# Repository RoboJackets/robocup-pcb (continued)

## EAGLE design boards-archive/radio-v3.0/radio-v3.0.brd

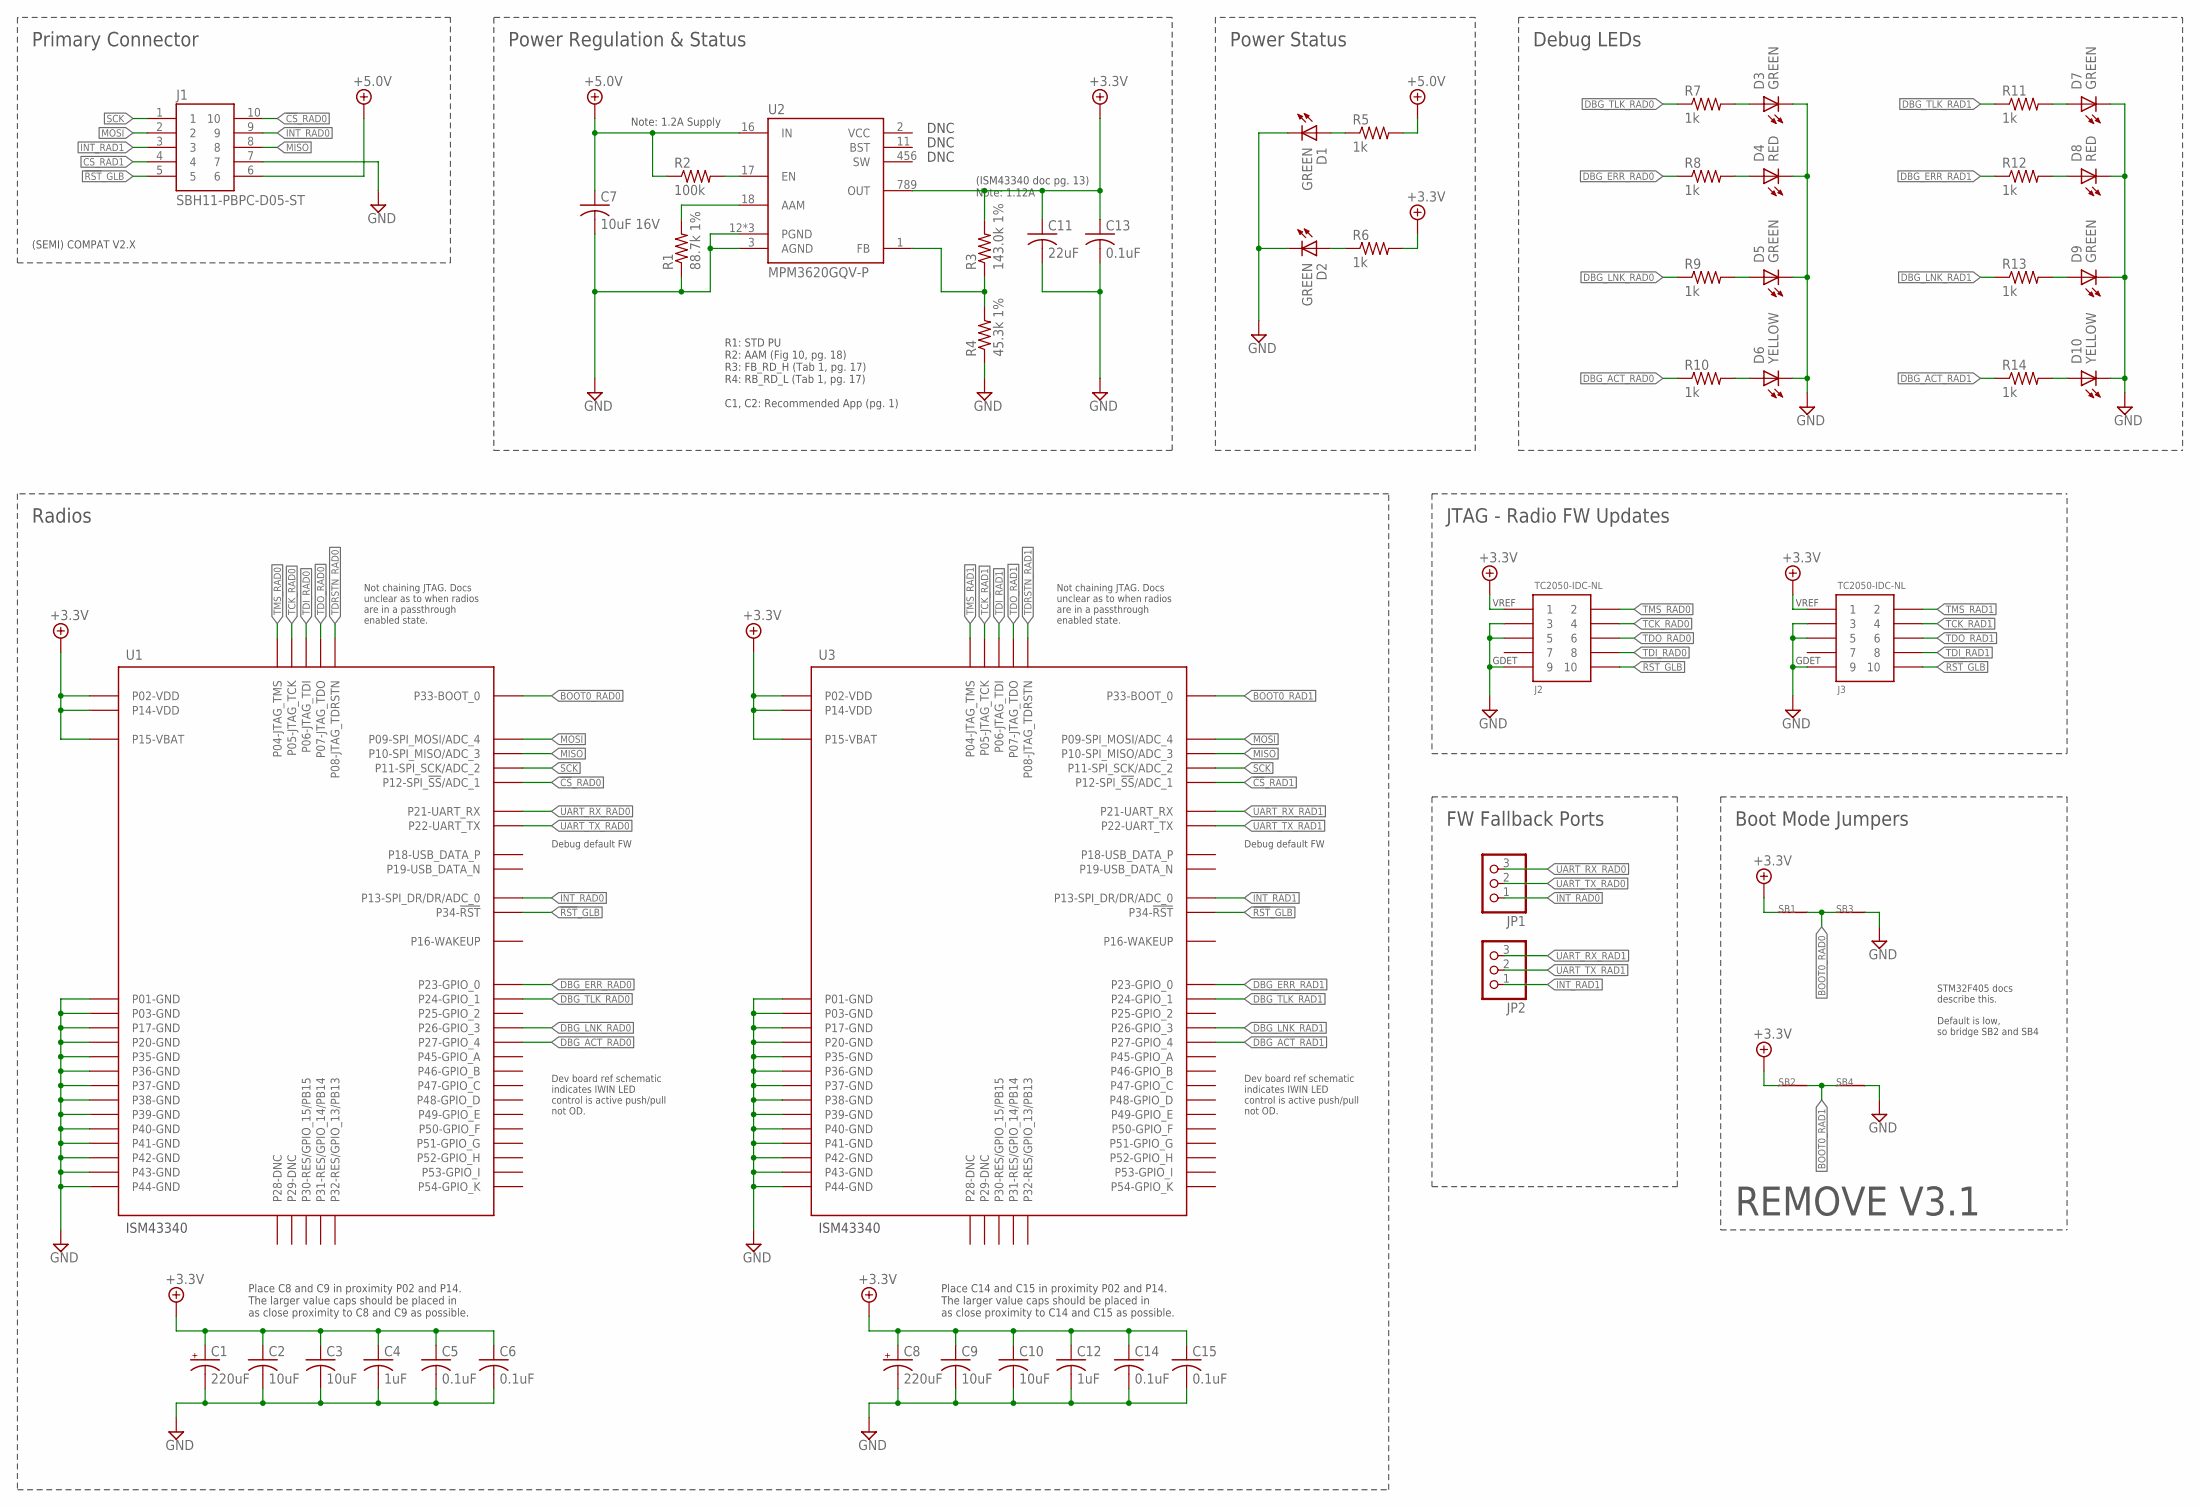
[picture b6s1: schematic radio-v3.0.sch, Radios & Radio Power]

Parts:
C1, C8: 220uF; ECA-0JM221-HGT_HORIZ
C2, C3, C9, C10: 10uF; C1210
C4, C12: 1uF; C0603
C5, C6, C13, C14, C15: 0.1uF; C0603
C7: 10uF 16V; C1210
C11: 22uF; C1210
D1, D2, D3, D5, D7, D9: GREEN; CHIP-LED0603
D4, D8: RED; CHIP-LED0603
D6, D10: YELLOW; CHIP-LED0603
J1: SBH11-PBPC-D05-ST; SFH11-*-D05-ST
J2, J3: TC2050-IDC-NL
JP1, JP2: PINHD-1X3; 1X03
R1: 88.7k 1%; R0603
R2: 100k; R0603
R3: 143.0k 1%; R0603
R4: 45.3k 1%; R0603
R5, R6, R7, R8, R9, R10, R11, R12, R13, R14: 1k; R0603
SB1, SB2, SB3, SB4: SOLDERBRIDGESB0603; SB0603
U1, U3: ISM43340
U2: MPM3620GQV-P

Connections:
3V3_PWR_IND: D2.A, R6.1
5V_PWR_IND: D1.A, R5.1
!CS!_RAD0: J1.10, U1.P$12 (P12-SPI_!SS!/ADC_1)
!CS!_RAD1: J1.4, U3.P$12 (P12-SPI_!SS!/ADC_1)
!RST!_GLB: J1.5, J2.P$10 (10), J3.P$10 (10), U1.P$34 (P34-!RST!), U3.P$34 (P34-!RST!)
+3.3V: C1.P$1 (+), C2.1, C3.1, C4.1, C5.1, C6.1, C8.P$1 (+), C9.1, C10.1, C11.1, C12.1, C13.1, C14.1, C15.1, J2.P$1 (1), J3.P$1 (1), R3.2, R6.2, SB1.1, SB2.1, U1.P$2 (P02-VDD), U1.P$14 (P14-VDD), U1.P$15 (P15-VBAT), U2.789 (OUT), U3.P$2 (P02-VDD), U3.P$14 (P14-VDD), U3.P$15 (P15-VBAT)
+5.0V: C7.1, J1.6, R2.1, R5.2, U2.16 (IN)
AAM: R1.2, U2.18 (AAM)
BOOT0_RAD0: SB1.2, SB3.1, U1.P$33 (P33-BOOT_0)
BOOT0_RAD1: SB2.2, SB4.1, U3.P$33 (P33-BOOT_0)
DBG_ACT_RAD0: R10.1, U1.P$27 (P27-GPIO_4)
DBG_ACT_RAD1: R14.1, U3.P$27 (P27-GPIO_4)
DBG_ERR_RAD0: R8.1, U1.P$23 (P23-GPIO_0)
DBG_ERR_RAD1: R12.1, U3.P$23 (P23-GPIO_0)
DBG_LNK_RAD0: R9.1, U1.P$26 (P26-GPIO_3)
DBG_LNK_RAD1: R13.1, U3.P$26 (P26-GPIO_3)
DBG_TLK_RAD0: R7.1, U1.P$24 (P24-GPIO_1)
DBG_TLK_RAD1: R11.1, U3.P$24 (P24-GPIO_1)
EN: R2.2, U2.17 (EN)
FB: R3.1, R4.2, U2.1 (FB)
GND: C1.P$2 (-), C2.2, C3.2, C4.2, C5.2, C6.2, C7.2, C8.P$2 (-), C9.2, C10.2, C11.2, C12.2, C13.2, C14.2, C15.2, D1.C (K), D2.C (K), D3.C (K), D4.C (K), D5.C (K), D6.C (K), D7.C (K), D8.C (K), D9.C (K), D10.C (K), J1.7, J2.P$3 (3), J2.P$5 (5), J2.P$9 (9), J3.P$3 (3), J3.P$5 (5), J3.P$9 (9), R1.1, R4.1, SB3.2, SB4.2, U1.P$1 (P01-GND), U1.P$3 (P03-GND), U1.P$17 (P17-GND), U1.P$20 (P20-GND), U1.P$35 (P35-GND), U1.P$36 (P36-GND), U1.P$37 (P37-GND), U1.P$38 (P38-GND), U1.P$39 (P39-GND), U1.P$40 (P40-GND), U1.P$41 (P41-GND), U1.P$42 (P42-GND), U1.P$43 (P43-GND), U1.P$44 (P44-GND), U2.3 (AGND), U2.12 (PGND), U2.13 (PGND), U2.14 (PGND), U3.P$1 (P01-GND), U3.P$3 (P03-GND), U3.P$17 (P17-GND), U3.P$20 (P20-GND), U3.P$35 (P35-GND), U3.P$36 (P36-GND), U3.P$37 (P37-GND), U3.P$38 (P38-GND), U3.P$39 (P39-GND), U3.P$40 (P40-GND), U3.P$41 (P41-GND), U3.P$42 (P42-GND), U3.P$43 (P43-GND), U3.P$44 (P44-GND)
INT_RAD0: J1.9, JP1.1, U1.P$13 (P13-SPI_DR/DR/ADC_0)
INT_RAD1: J1.3, JP2.1, U3.P$13 (P13-SPI_DR/DR/ADC_0)
MISO: J1.8, U1.P$10 (P10-SPI_MISO/ADC_3), U3.P$10 (P10-SPI_MISO/ADC_3)
MOSI: J1.2, U1.P$9 (P09-SPI_MOSI/ADC_4), U3.P$9 (P09-SPI_MOSI/ADC_4)
unnamed: D10.A, R14.2
unnamed: D9.A, R13.2
unnamed: D8.A, R12.2
unnamed: D7.A, R11.2
unnamed: D3.A, R7.2
unnamed: D4.A, R8.2
unnamed: D5.A, R9.2
unnamed: D6.A, R10.2
SCK: J1.1, U1.P$11 (P11-SPI_SCK/ADC_2), U3.P$11 (P11-SPI_SCK/ADC_2)
TCK_RAD0: J2.P$4 (4), U1.P$5 (P05-JTAG_TCK)
TCK_RAD1: J3.P$4 (4), U3.P$5 (P05-JTAG_TCK)
TDI_RAD0: J2.P$8 (8), U1.P$6 (P06-JTAG_TDI)
TDI_RAD1: J3.P$8 (8), U3.P$6 (P06-JTAG_TDI)
TDO_RAD0: J2.P$6 (6), U1.P$7 (P07-JTAG_TDO)
TDO_RAD1: J3.P$6 (6), U3.P$7 (P07-JTAG_TDO)
TDRSTN_RAD0: U1.P$8 (P08-JTAG_TDRSTN)
TDRSTN_RAD1: U3.P$8 (P08-JTAG_TDRSTN)
TMS_RAD0: J2.P$2 (2), U1.P$4 (P04-JTAG_TMS)
TMS_RAD1: J3.P$2 (2), U3.P$4 (P04-JTAG_TMS)
UART_RX_RAD0: JP1.3, U1.P$21 (P21-UART_RX)
UART_RX_RAD1: JP2.3, U3.P$21 (P21-UART_RX)
UART_TX_RAD0: JP1.2, U1.P$22 (P22-UART_TX)
UART_TX_RAD1: JP2.2, U3.P$22 (P22-UART_TX)

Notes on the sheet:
DNC
Primary Connector
Power Regulation & Status
Power Status
Note: 1.2A Supply
(ISM43340 doc pg. 13) Note: 1.12A
R1: STD PU R2: AAM (Fig 10, pg. 18) R3: FB_RD_H (Tab 1, pg. 17) R4: RB_RD_L (Tab 1, pg. 17) C1, C2: Recommended App (pg. 1)
(SEMI) COMPAT V2.X
Radios
Place C8 and C9 in proximity P02 and P14. The larger value caps should be placed in as close proximity to C8 and C9 as possible.
Place C14 and C15 in proximity P02 and P14. The larger value caps should be placed in as close proximity to C14 and C15 as possible.
Debug LEDs
VREF
GDET
JTAG - Radio FW Updates
Boot Mode Jumpers
FW Fallback Ports
Dev board ref schematic indicates IWIN LED control is active push/pull not OD.
Not chaining JTAG. Docs unclear as to when radios are in a passthrough enabled state.
Debug default FW
STM32F405 docs describe this. Default is low, so bridge SB2 and SB4
REMOVE V3.1

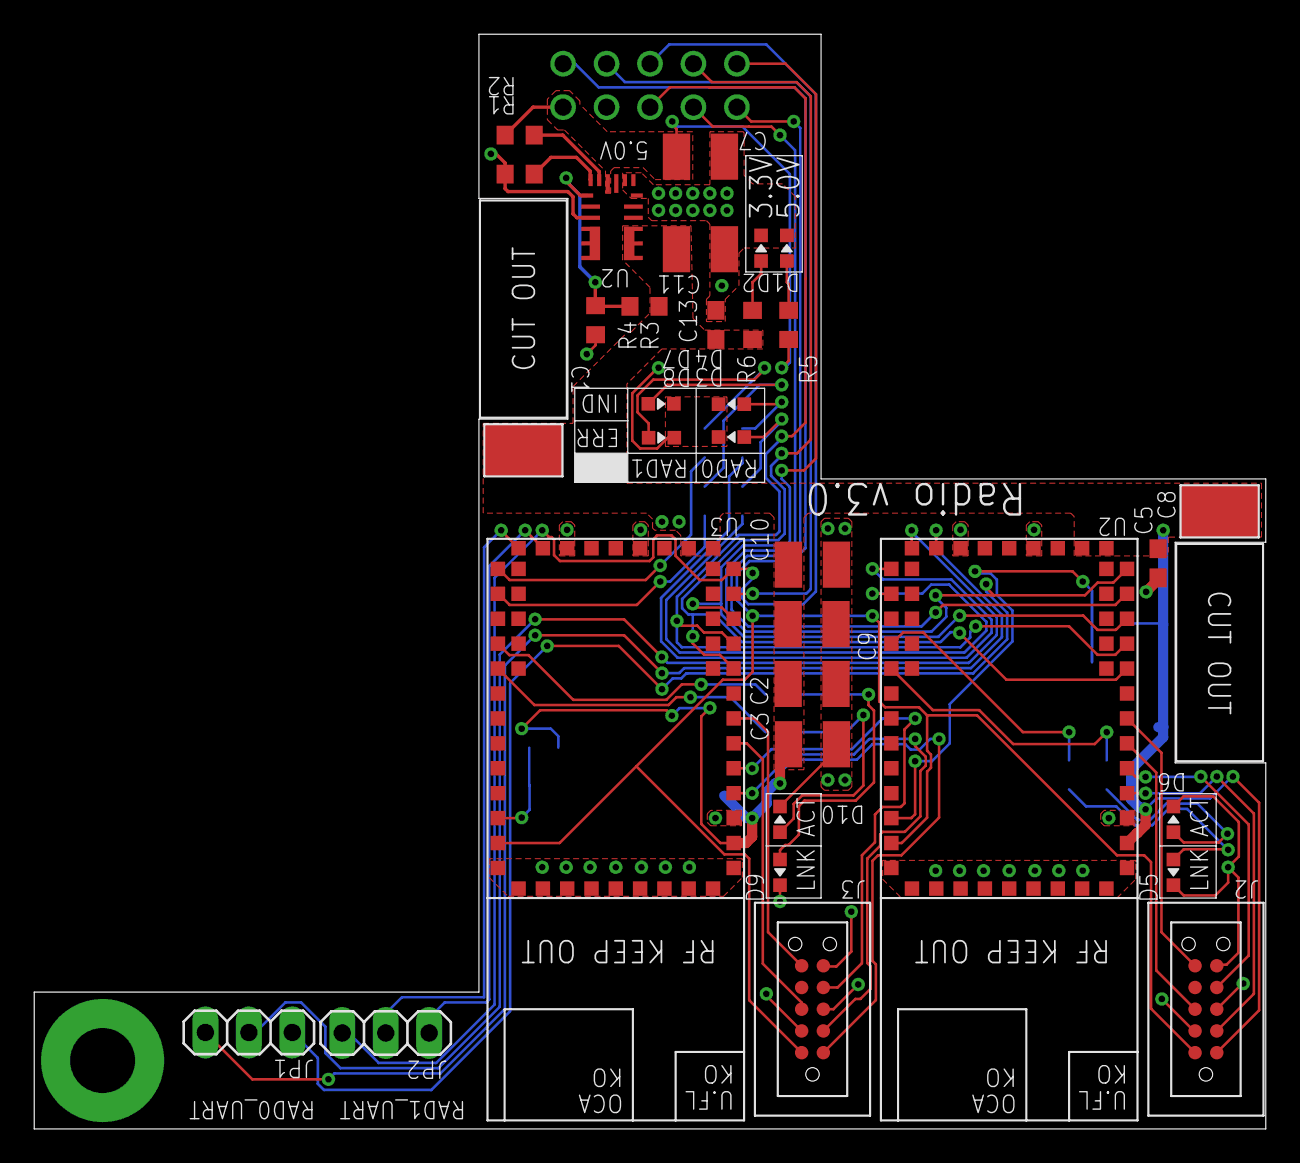
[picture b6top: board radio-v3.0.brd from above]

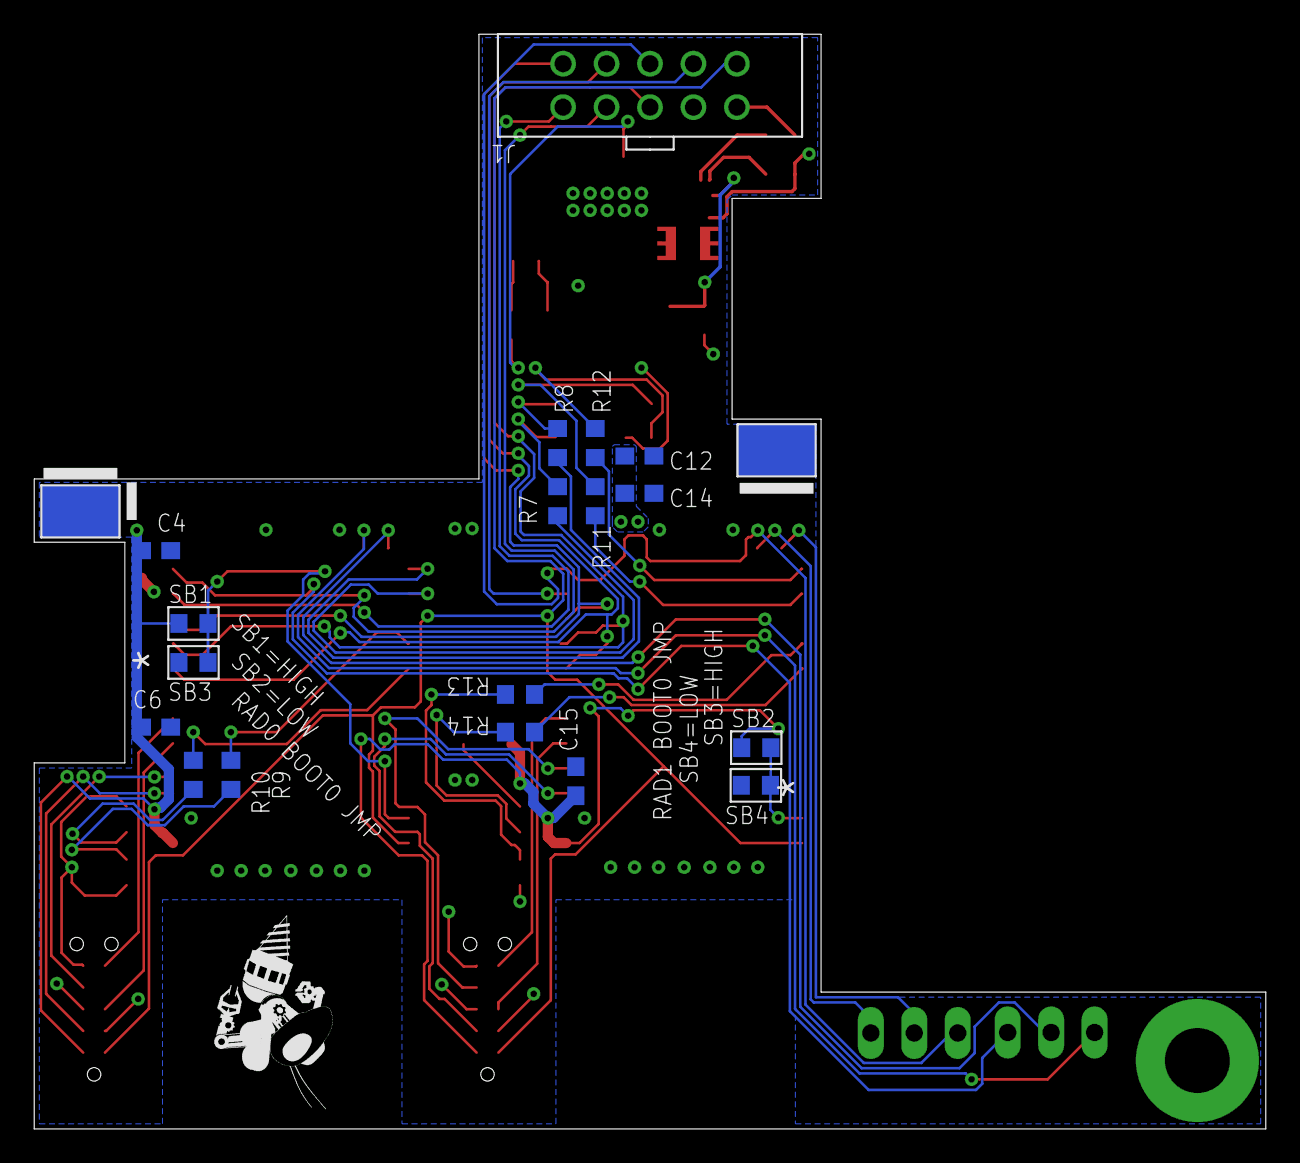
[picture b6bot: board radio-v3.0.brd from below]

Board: 2 copper layers, 72.0 x 64.0 mm, 52 parts (19 on the bottom side), 46 nets.

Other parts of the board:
U$1: ROBOBUZZ_0.6X

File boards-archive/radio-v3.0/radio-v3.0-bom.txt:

Partlist exported from /home/robojackets/robocup-pcb/boards/radio-v3.0/radio-v3.0.sch at 3/22/19 1:34 PM

Qty Value              Device             Package              Parts                                       Description                DIGIKEY       MPN                  SPICEPREFIX VALUE 
2                      PINHD-1X3          1X03                 JP1, JP2                                    PIN HEADER                                                                      
5   0.1uF              C-USC0603          C0603                C5, C6, C13, C14, C15                       CAPACITOR, American symbol                                    C                 
1   100k               R-US_R0603         R0603                R2                                          RESISTOR, American symbol                                                       
4   10uF               C-USC1210          C1210                C2, C3, C9, C10                             CAPACITOR, American symbol                                    C                 
1   10uF 16V           C-USC1210          C1210                C7                                          CAPACITOR, American symbol                                    C                 
1   143.0k 1%          R-US_R0603         R0603                R3                                          RESISTOR, American symbol                                     R                 
10  1k                 R-US_R0603         R0603                R5, R6, R7, R8, R9, R10, R11, R12, R13, R14 RESISTOR, American symbol                                                       
2   1uF                C-USC0603          C0603                C4, C12                                     CAPACITOR, American symbol                                    C                 
2   220uF              ECA-0JM221         ECA-0JM221-HGT_HORIZ C1, C8                                                                                                                      
1   22uF               C-USC1210          C1210                C11                                         CAPACITOR, American symbol                                    C                 
1   45.3k 1%           R-US_R0603         R0603                R4                                          RESISTOR, American symbol                                     R                 
1   88.7k 1%           R-US_R0603         R0603                R1                                          RESISTOR, American symbol                                                       
6   GREEN              LED-SMD-GREEN      CHIP-LED0603         D1, D2, D3, D5, D7, D9                                                 160-1446-1-ND LTST-C191KGKT                    GREEN 
2   ISM43340           ISM43340           ISM43340             U1, U3                                                                                                                      
1   MPM3620GQV-P       MPM3620GQV-P       MPM3620GQV-P         U2                                                                                                                          
2   RED                LED-SMD-RED        CHIP-LED0603         D4, D8                                                                 160-1447-1-ND LTST-C191KRKT                    RED   
1   SBH11-PBPC-D05-ST  SBH11-PBPC-D05-ST  SFH11-*-D05-ST       J1                                                                     S9194-ND      SFH11-PBPC-D05-ST-BK                   
4   SOLDERBRIDGESB0603 SOLDERBRIDGESB0603 SB0603               SB1, SB2, SB3, SB4                                                                                                          
2   TC2050-IDC-NL      TC2050-IDC-NL      TC2050-IDC-NL        J2, J3                                                                                                                      
2   YELLOW             LED-SMD-YELLOW     CHIP-LED0603         D6, D10                                                                160-1448-1-ND LTST-C191KSKT                    YELLOW
